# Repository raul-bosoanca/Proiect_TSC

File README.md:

# Proiect_TSC

BOM (Bill of Materials):

| Item | Product Link | Datasheet Link |
|------|-------------|---------------|
| 112A-TAAR-R03 | [Product](https://store.comet.srl.ro/Catalogue/Product/43497/) | [Datasheet](https://store.comet.bg/download-file.php?id=27596) |
| BD5229G-TR | [Product](https://store.comet.srl.ro/Catalogue/Product/43497/) | [Datasheet](https://datasheet.datasheetarchive.com/originals/distributors/Datasheets_SAMA/f2b9741ef86007909f138d561a359946.pdf) |
| Capacitor 0402 | [Product](https://store.comet.srl.ro/Catalogue/Product/43497/) | [Datasheet](https://componentsearchengine.com/Datasheets/2/CC0402MRX5R5BB106.pdf) |
| CPH3225A | [Product](https://store.comet.srl.ro/Catalogue/Product/43497/) | [Datasheet](https://www.snapeda.com/parts/CPH3225A/Seiko%20Instruments/datasheet/) |
| DS3231SN RTC | [Product](https://store.comet.srl.ro/Catalogue/Product/43497/) | [Datasheet](https://www.snapeda.com/parts/DS3231SN%23/Analog%20Devices/datasheet/) |
| ESP32 WROVER 0805 Capacitor | [Product](https://store.comet.srl.ro/Catalogue/Product/43497/) | [Datasheet](https://ro.mouser.com/datasheet/2/40/schottky-3165252.pdf) |
| ESP32 WROVER BME680 Sensor | [Product](https://store.comet.srl.ro/Catalogue/Product/43497/) | [Datasheet](https://www.snapeda.com/parts/BME680/Bosch%20Sensortec/datasheet/) |
| ESP32 WROVER MCP73831 Power Management | [Product](https://store.comet.srl.ro/Catalogue/Product/43497/) | [Datasheet](https://eu.mouser.com/datasheet/2/268/MCP73831_Family_Data_Sheet_DS20001984H-3441711.pdf) |
| ESP32 WROVER P-Channel MOSFET | [Product](https://store.comet.srl.ro/Catalogue/Product/43497/) | [Datasheet](https://www.diodes.com/assets/Datasheets/DMG2305UX.pdf) |
| ESP32C6 Varistor 1812 | [Product](https://store.comet.srl.ro/Catalogue/Product/43497/) | [Datasheet](https://www.tdk-electronics.tdk.com/inf/75/db/CTVS_14/Surge_protection_series.pdf) |
| ESP32-C6 WROOM-1-N8 | [Product](https://store.comet.srl.ro/Catalogue/Product/43497/) | [Datasheet](https://www.snapeda.com/parts/ESP32-C6-WROOM-1-N8/Espressif%20Systems/datasheet/) |
| FH34SRJ-24S-0.5SH Connector | [Product](https://store.comet.srl.ro/Catalogue/Product/43497/) | [Datasheet](https://www.hirose.com/en/product/document?clcode=CL0580-1255-6-99&productname=FH34SRJ-24S-0.5SH(99)&series=FH34SRJ&documenttype=2DDrawing&lang=en&documentid=0000990903) |
| LED Chip 0603 | [Product](https://store.comet.srl.ro/Catalogue/Product/43497/) | [Datasheet](https://www.snapeda.com/parts/KP-1608SURCK/Kingbright/datasheet/) |
| MAX17048G+T10 Battery Fuel Gauge | [Product](https://store.comet.srl.ro/Catalogue/Product/43497/) | [Datasheet](https://www.snapeda.com/parts/MAX17048G+T10/Analog%20Devices/datasheet/) |
| MBR0530 Schottky Diode | [Product](https://store.comet.srl.ro/Catalogue/Product/43497/) | [Datasheet](https://www.snapeda.com/parts/MBR0530/ON%20Semiconductor/datasheet/) |
| PGB1010603MR Inductor | [Product](https://store.comet.srl.ro/Catalogue/Product/43497/) | [Datasheet](https://www.snapeda.com/parts/PGB1010603MR/Littelfuse%20Inc./datasheet/) |
| QWIIC Connector | [Product](https://store.comet.srl.ro/Catalogue/Product/43497/) | [Datasheet](https://www.youtube.com/watch?v=dQw4w9WgXcQ) |
| RCL CPOL 3528 | [Product](https://store.comet.srl.ro/Catalogue/Product/43497/) | [Datasheet](https://s3.amazonaws.com/snapeda/datasheet/TAJB475K025RNJ_AVX.pdf) |
| SI1308EDL-T1-GE3 MOSFET | [Product](https://store.comet.srl.ro/Catalogue/Product/43497/) | [Datasheet](https://www.youtube.com/watch?v=dQw4w9WgXcQ) |
| SJ | [Product](https://store.comet.srl.ro/Catalogue/Product/43497/) | [Datasheet](https://www.youtube.com/watch?v=dQw4w9WgXcQ) |
| TPTP20R | [Product](https://store.comet.srl.ro/Catalogue/Product/43497/) | [Datasheet](https://easyeda.com/component/7524403feb2642ac9f9f26dfb93ceacf) |
| USB4110-GF-A USB Hub | [Product](https://store.comet.srl.ro/Catalogue/Product/43497/) | [Datasheet](https://gct.co/files/drawings/usb4110.pdf) |
| USBLC6-2SC6Y USB Surge Protection | [Product](https://store.comet.srl.ro/Catalogue/Product/43497/) | [Datasheet](https://www.snapeda.com/parts/USBLC6-2SC6Y/STMicroelectronics/datasheet/) |
| XC6220A331MR-G Voltage Regulator | [Product](https://store.comet.srl.ro/Catalogue/Product/43497/) | [Datasheet](https://product.torexsemi.com/system/files/series/xc6220.pdf) |

  Hardware Components:

  ESP32-C3-WROOM:
    
    Wi-Fi/BLE connectivity
    Supports SPI, I2C, and UART communication
    Operates at 3.3V, powered by an LDO regulator

  USB-C - Charging & USB communication
  
  MCP73832 - LiPo battery charging management
  
  LDO 3.3V - Supplies power to ESP32 and peripherals
  
  DC/DC 5V - Provides 5V for sensors
  
  BME680 - Enveroment sensor

ESP32 PINOUT:

    IO0 - RTC INT Signal
    IO1 - CLOCK Signal
    IO2 - SPI MISO Signal
    IO3 - EPD BUSY Signal
    IO4 - SD Card Chip Select
    IO5 - EPD DC Signal
    IO6 - SPI SCK Signal
    IO7 - SPI MOSI Signal
    IO9 - BOOT Button Signal
    IO10 - EPD Chip Select
    IO11 - Flash NOR Memory Chip Select
    IO12 - USB D+ Signal
    IO13 - USB D- Signal
    IO15 - CHANGE Button Signal
    GPIO16 - UART TX
    GPIO17 - UART RX
    IO18 - RTC RESET Signal
    IO19 - I2C Sensor VDDIO Signal
    IO20 - EPD 3V3
    IO21 - I2C SDA Signal
    IO22 - I2C SCL Signal
    IO23 - EPD RESET Signal

Note : On the final 3D models i did not render the top and buttom ground planes because the working pc did not have the power to render them

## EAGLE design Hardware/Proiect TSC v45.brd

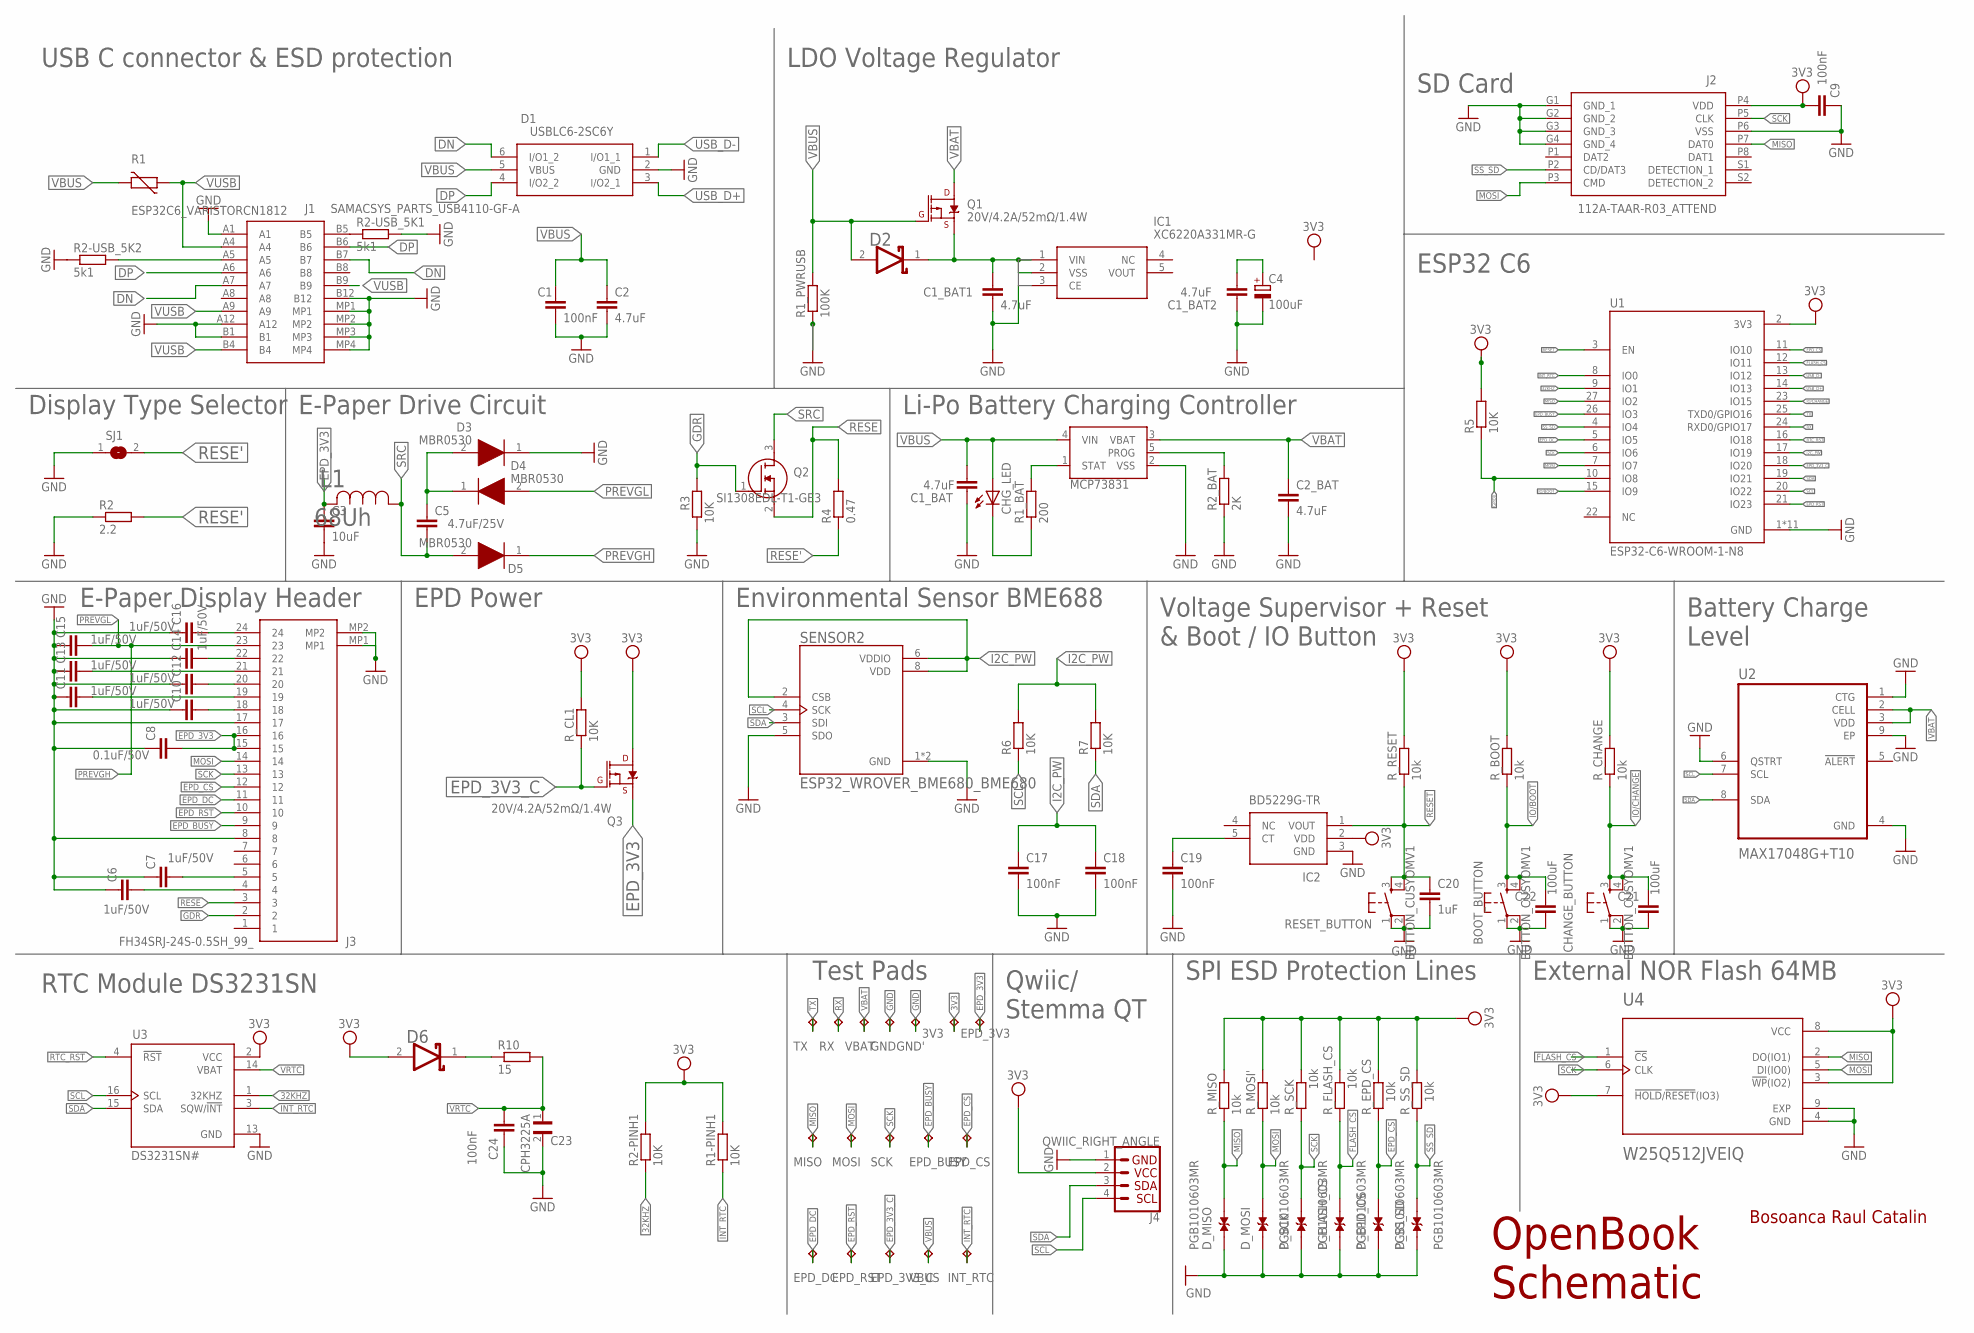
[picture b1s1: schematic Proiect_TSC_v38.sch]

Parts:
3V3: TPTP20R; TP20R
BOOT_BUTTON: BUTTON_CUSYOMV1; MYBUTTON
C1, C9, C17, C18, C19, C23: 100nF; EAGLE-LTSPICE_C0402
C1_BAT, C1_BAT1, C1_BAT2, C2, C2_BAT: 4.7uF; EAGLE-LTSPICE_C0402
C3: 10uF; EAGLE-LTSPICE_C0402
C4: 100uF; RCL_CT3528
C5: 4.7uF/25V; EAGLE-LTSPICE_C0402
C6, C7, C10, C11, C12, C13, C14, C15, C16: 1uF/50V; EAGLE-LTSPICE_C0402
C8: 0.1uF/50V; EAGLE-LTSPICE_C0402
C20: 1uF; EAGLE-LTSPICE_C0402
C21, C22: 100uF; EAGLE-LTSPICE_C0402
C24: CPH3225A; CAPCP3225X100N
CHANGE_BUTTON: BUTTON_CUSYOMV1; MYBUTTON
CHG_LED: ADAFRUIT_LEDCHIP-LED0603; ADAFRUIT_CHIP-LED0603
D1: USBLC6-2SC6Y; SOT95P280X145-6N
D2, D6: ESP32_WROVER_AVX---SD0805S020S1R0_AVX_SD0805S020S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; ESP32_WROVER_AVX---SD0805S020S1R0_AVX_SD0805S020S1R0_0
D3, D4, D5: MBR0530; SOD3716X135N
D_EPD_CS: PGB1010603MR; ESP32_WROVER_AVX---SD0805S020S1R0_AVX_SD0805S020S1R0_0
D_FLASH_CS: PGB1010603MR; ESP32_WROVER_AVX---SD0805S020S1R0_AVX_SD0805S020S1R0_0
D_MISO: PGB1010603MR; ESP32_WROVER_AVX---SD0805S020S1R0_AVX_SD0805S020S1R0_0
D_MOSI: PGB1010603MR; ESP32_WROVER_AVX---SD0805S020S1R0_AVX_SD0805S020S1R0_0
D_SCK: PGB1010603MR; ESP32_WROVER_AVX---SD0805S020S1R0_AVX_SD0805S020S1R0_0
D_SS_SD: PGB1010603MR; ESP32_WROVER_AVX---SD0805S020S1R0_AVX_SD0805S020S1R0_0
EPD_3V3, EPD_3V3_C: TPTP20R; TP20R
EPD_BUSY: TPTP20R; TP20R
EPD_CS: TPTP20R; TP20R
EPD_DC: TPTP20R; TP20R
EPD_RST: TPTP20R; TP20R
GND: TPTP20R; TP20R
GND': TPTP20R; TP20R
IC1: XC6220A331MR-G; SOT95P280X125-5N
IC2: BD5229G-TR; SOT95P280X125-5N
INT_RTC: TPTP20R; TP20R
J1: SAMACSYS_PARTS_USB4110-GF-A; SAMACSYS_PARTS_USB4110GFA
J2: 112A-TAAR-R03_ATTEND; 112ATAARR03ATTEND
J3: FH34SRJ-24S-0.5SH_99_; FH34SRJ24S05SH99
J4: QWIIC_RIGHT_ANGLE; JST04_1MM_RA
L1: 68Uh; IND_4828-WE-TPC_WRE
MCP73831: ESP32_WROVER_SPARKFUN-IC-POWER_MCP73831; ESP32_WROVER_SPARKFUN-IC-POWER_SOT23-5
MISO: TPTP20R; TP20R
MOSI: TPTP20R; TP20R
Q1, Q3: 20V/4.2A/52mΩ/1.4W; ESP32_WROVER_SPARKFUN-DISCRETESEMI_SOT23-3
Q2: SI1308EDL-T1-GE3; SOT65P210X110-3N
R1: ESP32C6_VARISTORCN1812; ESP32C6_VARISTOR_CT/CN1812
R1-PINH1, R2-PINH1, R3, R5, R6, R7: 10K; EAGLE-LTSPICE_C0402
R1_BAT: 200; EAGLE-LTSPICE_C0402
R1_PWRUSB: 100K; EAGLE-LTSPICE_C0402
R2: 2.2; EAGLE-LTSPICE_C0402
R2-USB_5K1, R2-USB_5K2: 5k1; EAGLE-LTSPICE_C0402
R2_BAT: 2K; EAGLE-LTSPICE_C0402
R4: 0.47; EAGLE-LTSPICE_C0402
R10: 15; EAGLE-LTSPICE_C0402
RESET_BUTTON: BUTTON_CUSYOMV1; MYBUTTON
RX: TPTP20R; TP20R
R_BOOT: 10k; EAGLE-LTSPICE_C0402
R_CHANGE: 10k; EAGLE-LTSPICE_C0402
R_CL1: 10K; EAGLE-LTSPICE_C0402
R_EPD_CS: 10k; EAGLE-LTSPICE_C0402
R_FLASH_CS: 10k; EAGLE-LTSPICE_C0402
R_MISO: 10k; EAGLE-LTSPICE_C0402
R_MOSI': 10k; EAGLE-LTSPICE_C0402
R_RESET: 10k; EAGLE-LTSPICE_C0402
R_SCK: 10k; EAGLE-LTSPICE_C0402
R_SS_SD: 10k; EAGLE-LTSPICE_C0402
SCK: TPTP20R; TP20R
SENSOR2: ESP32_WROVER_BME680_BME680; ESP32_WROVER_BME680_PSON80P300X300X100-8N
SJ1: SJ
TX: TPTP20R; TP20R
U1: ESP32-C6-WROOM-1-N8; XCVR_ESP32-C6-WROOM-1-N8
U2: MAX17048G+T10; SON50P200X200X80-9N
U3: DS3231SN#; SOIC127P1032X265-16N
U4: W25Q512JVEIQ; SON127P600X800X80-9N
VBAT: TPTP20R; TP20R
VBUS: TPTP20R; TP20R

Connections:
3V3: 3V3.TP, C9.1, D6.2 (ANODE), IC2.2 (VDD), J2.P4 (VDD), J4.2, Q3.3 (D), R1-PINH1.2, R2-PINH1.2, R5.2, R_BOOT.2, R_CHANGE.2, R_CL1.2, R_EPD_CS.2, R_FLASH_CS.2, R_MISO.2, R_MOSI'.2, R_RESET.2, R_SCK.2, R_SS_SD.2, U1.2 (3V3), U3.2 (VCC), U4.3 (!WP!(IO2)), U4.7 (!HOLD!/!RESET!(IO3)), U4.8 (VCC)
32KHZ: R2-PINH1.1, U1.9 (IO1), U3.1 (32KHZ)
DN: D1.6 (I/O1_2), J1.A7, J1.B7
DP: D1.4 (I/O2_2), J1.A6, J1.B6
EPD_3V3: C3.1, C8.2, EPD_3V3.TP, J3.15, J3.16, L1.2, Q3.2 (S)
EPD_3V3_C: EPD_3V3_C.TP, Q3.1 (G), R_CL1.1, U1.18 (IO20)
EPD_BUSY: EPD_BUSY.TP, J3.9, U1.26 (IO3)
EPD_CS: D_EPD_CS.2, EPD_CS.TP, J3.12, R_EPD_CS.1, U1.11 (IO10)
EPD_DC: EPD_DC.TP, J3.11, U1.5 (IO5)
EPD_RST: EPD_RST.TP, J3.10, U1.21 (IO23)
FLASH_CS: D_FLASH_CS.2, R_FLASH_CS.1, U1.12 (IO11), U4.1 (!CS)
GDR: J3.2, Q2.1 (G), R3.2
GND: BOOT_BUTTON.1, BOOT_BUTTON.2, C1.2, C1_BAT.2, C1_BAT1.2, C1_BAT2.2, C2.2, C2_BAT.2, C3.2, C4.-, C6.1, C7.1, C8.1, C9.2, C10.1, C11.1, C12.1, C13.1, C14.1, C15.1, C16.1, C17.2, C18.2, C19.2, C20.2, C21.2, C22.2, C23.2, C24.2, CHANGE_BUTTON.1, CHANGE_BUTTON.2, D1.2 (GND), D3.1 (K), D_EPD_CS.1, D_FLASH_CS.1, D_MISO.1, D_MOSI.1, D_SCK.1, D_SS_SD.1, GND.TP, GND'.TP, IC2.3 (GND), J1.A1, J1.A12, J1.B1, J1.B12, J1.MP1, J1.MP2, J1.MP3, J1.MP4, J2.G1 (GND_1), J2.G2 (GND_2), J2.G3 (GND_3), J2.G4 (GND_4), J2.P6 (VSS), J3.8, J3.17, J3.MP1, J3.MP2, J4.1, MCP73831.2 (VSS), R1_PWRUSB.1, R2.1, R2-USB_5K1.2, R2-USB_5K2.1, R2_BAT.1, R3.1, RESET_BUTTON.1, RESET_BUTTON.2, SENSOR2.1 (GND), SENSOR2.5 (SDO), SENSOR2.7 (GND), SJ1.1, U1.1 (GND), U1.28 (GND), U1.29_1 (GND), U1.29_2 (GND), U1.29_3 (GND), U1.29_4 (GND), U1.29_5 (GND), U1.29_6 (GND), U1.29_7 (GND), U1.29_8 (GND), U1.29_9 (GND), U2.1 (CTG), U2.4 (GND), U2.6 (QSTRT), U2.9 (EP), U3.13 (GND), U4.4 (GND), U4.9 (EXP)
GPIO8: R5.1, U1.10 (IO8)
I2C_PW: C17.1, C18.1, R6.2, R7.2, SENSOR2.2 (CSB), SENSOR2.6 (VDDIO), SENSOR2.8 (VDD), U1.17 (IO19)
INT_RTC: INT_RTC.TP, R1-PINH1.1, U1.8 (IO0), U3.3 (SQW/!INT)
IO/BOOT: BOOT_BUTTON.3, BOOT_BUTTON.4, C22.1, R_BOOT.1, U1.15 (IO9)
IO/CHANGE: C21.1, CHANGE_BUTTON.3, CHANGE_BUTTON.4, R_CHANGE.1, U1.23 (IO15)
MISO: D_MISO.2, J2.P7 (DAT0), MISO.TP, R_MISO.1, U1.27 (IO2), U4.2 (DO(IO1))
MOSI: D_MOSI.2, J2.P3 (CMD), J3.14, MOSI.TP, R_MOSI'.1, U1.7 (IO7), U4.5 (DI(IO0))
unnamed: C5.1, D3.2 (A), D4.1 (K)
unnamed: CHG_LED.C, R1_BAT.1
unnamed: J1.B5, R2-USB_5K1.1
unnamed: MCP73831.1 (STAT), R1_BAT.2
unnamed: MCP73831.5 (PROG), R2_BAT.2
unnamed: C6.2, J3.4
unnamed: C19.1, IC2.5 (CT)
unnamed: J1.A5, R2-USB_5K2.2
unnamed: D6.1 (CATHODE), R10.1
unnamed: C7.2, J3.5
unnamed: C10.2, J3.18
unnamed: C1_BAT1.1, D2.1 (CATHODE), IC1.1 (VIN), IC1.2 (VSS), Q1.2 (S)
unnamed: C11.2, J3.19
unnamed: C12.2, J3.20
unnamed: C1_BAT2.1, C4.+
unnamed: C14.2, J3.22
unnamed: C16.2, J3.24
PREVGH: C13.2, D5.1 (K), J3.21
PREVGL: C15.2, D4.2 (A), J3.23
RESE: J3.3, Q2.2 (S), R4.2
RESE': R2.2, R4.1, SJ1.2
RESET: C20.1, IC2.1 (VOUT), RESET_BUTTON.3, RESET_BUTTON.4, R_RESET.1, U1.3 (EN)
RTC_RST: U1.16 (IO18), U3.4 (!RST)
RX: RX.TP, U1.24 (RXD0/GPIO17)
SCK: D_SCK.2, J2.P5 (CLK), J3.13, R_SCK.1, SCK.TP, U1.6 (IO6), U4.6 (CLK)
SCL: J4.4, R6.1, SENSOR2.4 (SCK), U1.20 (IO22), U2.7 (SCL), U3.16 (SCL)
SDA: J4.3, R7.1, SENSOR2.3 (SDI), U1.19 (IO21), U2.8 (SDA), U3.15 (SDA)
SRC: C5.2, D5.2 (A), L1.1, Q2.3 (D)
SS_SD: D_SS_SD.2, J2.P2 (CD/DAT3), R_SS_SD.1, U1.4 (IO4)
TX: TX.TP, U1.25 (TXD0/GPIO16)
USB_D+: D1.3 (I/O2_1), U1.14 (IO13)
USB_D-: D1.1 (I/O1_1), U1.13 (IO12)
VBAT: C2_BAT.1, MCP73831.3 (VBAT), Q1.3 (D), U2.2 (CELL), U2.3 (VDD), VBAT.TP
VBUS: C1.1, C1_BAT.1, C2.1, CHG_LED.A, D1.5 (VBUS), D2.2 (ANODE), MCP73831.4 (VIN), Q1.1 (G), R1.2, R1_PWRUSB.2, VBUS.TP
VRTC: C23.1, C24.1, R10.2, U3.14 (VBAT)
VUSB: J1.A4, J1.A9, J1.B4, J1.B9, R1.1

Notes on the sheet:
USB C connector & ESD protection
LDO Voltage Regulator
SD Card
Display Type Selector
E-Paper Drive Circuit
Li-Po Battery Charging Controller
ESP32 C6
E-Paper Display Header
EPD Power
Environmental Sensor BME688
Voltage Supervisor + Reset & Boot / IO Button
Battery Charge Level
RTC Module DS3231SN
Test Pads
Qwiic/ Stemma QT
SPI ESD Protection Lines
External NOR Flash 64MB
Bosoanca Raul Catalin
OpenBook Schematic

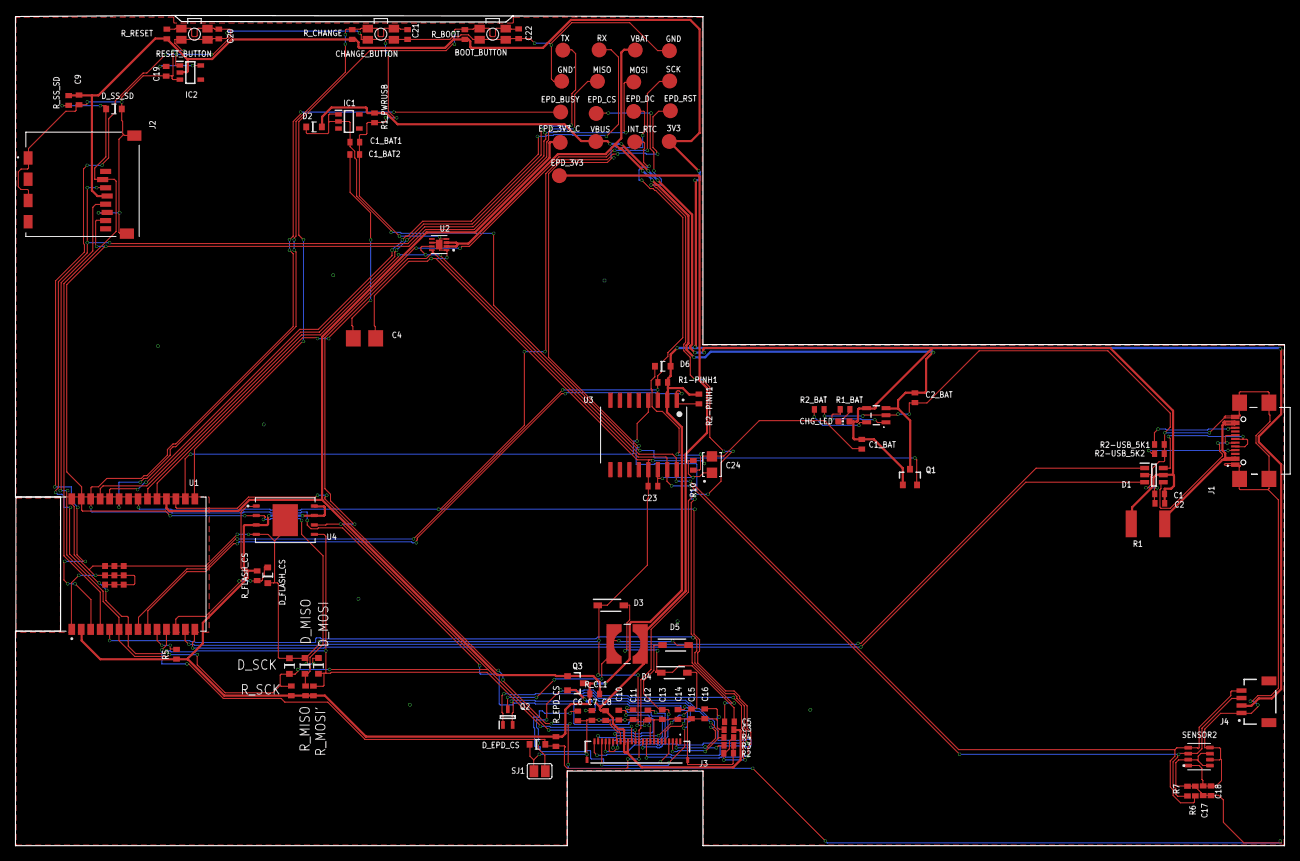
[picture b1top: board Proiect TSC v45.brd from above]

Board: 2 copper layers, 170.2 x 111.3 mm, 103 parts (0 on the bottom side), 56 nets.

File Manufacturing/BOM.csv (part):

Qty,Value,Device,Package,Parts,Description,ARROW_PART_NUMBER,ARROW_PRICE-STOCK,AVAILABILITY,CENTROID_NOT_SPECIFIED,CHECK_PRICES,COPYRIGHT,DATASHEET,DESCRIPTION,DIGIKEY_DESCRIPTION,DIGIKEY_PART_NUMBER,HEIGHT,LEAD_FREE,MANUFACTURER_NAME,MANUFACTURER_PART_NUMBER,MF,MFR_NAME,MOUSER_PART_NUMBER,MOUSER_PRICE-STOCK,MOUSER_TESTING_PART_NUMBER,MOUSER_TESTING_PRICE-STOCK,MP,MPN,PACKAGE,POPULARITY,PREFIX,PRICE,PROD_ID,PURCHASE-URL,ROHS,SNAPEDA_LINK,SPICEMODEL,SPICEPREFIX,TEMPERATURE_RANGE_HIGH,TEMPERATURE_RANGE_LOW,TP_SIGNAL_NAME,VALUE
1,,ADAFRUIT_LEDCHIP-LED0603,ADAFRUIT_CHIP-LED0603,CHG_LED,LED,,,,,,,,,,,,,,,,,,,,,,,,,,,,,,,,,,,,
1,,SJ,SJ,SJ1,"SMD solder JUMPER",,,,,,,,,,,,,,,,,,,,,,,,3,,,,,,,,,,,,
1,0.47,ESP32_WROVER_EAGLE-LTSPICE_RR0402,EAGLE-LTSPICE_C0402,R4,"RESISTOR, European symbol",,,,,,,,,,,,,,,,,,,,,,,,,,,,,,,NONE,R,,,,
1,100K,ESP32_WROVER_EAGLE-LTSPICE_RR0402,EAGLE-LTSPICE_C0402,R1_PWRUSB,"RESISTOR, European symbol",,,,,,,,,,,,,,,,,,,,,,,,,,,,,,,NONE,R,,,,
4,100nF,EAGLE-LTSPICE_CC0402,EAGLE-LTSPICE_C0402,"C17, C18, C19, C23","CAPACITOR, European symbol",,,,,,,,,,,,,,,,,,,,,,,,,,,,,,,NONE,C,,,,
2,100nF,ESP32_WROVER_EAGLE-LTSPICE_CC0402,EAGLE-LTSPICE_C0402,"C1, C9","CAPACITOR, European symbol",,,,,,,,,,,,,,,,,,,,,,,,,,,,,,,NONE,C,,,,
2,100uF,EAGLE-LTSPICE_CC0402,EAGLE-LTSPICE_C0402,"C21, C22","CAPACITOR, European symbol",,,,,,,,,,,,,,,,,,,,,,,,,,,,,,,NONE,C,,,,
1,100uF,RCL_CPOL-EUCT3528,RCL_CT3528,C4,"POLARIZED CAPACITOR, European symbol",,,,,,,,,,,,,,,,,,,,,,,,0,,,,,,,,C,,,,
7,10K,ESP32_WROVER_EAGLE-LTSPICE_RR0402,EAGLE-LTSPICE_C0402,"R1-PINH1, R2-PINH1, R3, R5, R6, R7, R_CL1","RESISTOR, European symbol",,,,,,,,,,,,,,,,,,,,,,,,,,,,,,,NONE,R,,,,
9,10k,ESP32_WROVER_EAGLE-LTSPICE_RR0402,EAGLE-LTSPICE_C0402,"R_BOOT, R_CHANGE, R_EPD_CS, R_FLASH_CS, R_MISO, R_MOSI', R_RESET, R_SCK, R_SS_SD","RESISTOR, European symbol",,,,,,,,,,,,,,,,,,,,,,,,,,,,,,,NONE,R,,,,
1,10uF,ESP32_WROVER_EAGLE-LTSPICE_CC0402,EAGLE-LTSPICE_C0402,C3,"CAPACITOR, European symbol",,,,,,,,,,,,,,,,,,,,,,,,,,,,,,,NONE,C,,,,
1,112A-TAAR-R03_ATTEND,112A-TAAR-R03_ATTEND,112ATAARR03ATTEND,J2,"Micro SD Card Socket, Push-Push Type, Top Mount, SMT, H=1.83mm, 10u",,,,,,,,"Micro SD Card Socket"," Push-Push Type"," Top Mount"," SMT"," H=1.83mm"," 10u",,,1.9mm,,ATTEND,"112A-TAAR-R03 ATTEND",,,,,,,,,,,,,,,,,
1,15,ESP32_WROVER_EAGLE-LTSPICE_RR0402,EAGLE-LTSPICE_C0402,R10,"RESISTOR, European symbol",,,,,,,,,,,,,,,,,,,,,,,,,,,,,,,NONE,R,,,,
1,1uF,EAGLE-LTSPICE_CC0402,EAGLE-LTSPICE_C0402,C20,"CAPACITOR, European symbol",,,,,,,,,,,,,,,,,,,,,,,,,,,,,,,NONE,C,,,,
10,1uF/50V,EAGLE-LTSPICE_CC0402,EAGLE-LTSPICE_C0402,"C6, C7, C8, C10, C11, C12, C13, C14, C15, C16","CAPACITOR, European symbol",,,,,,,,,,,,,,,,,,,,,,,,,,,,,,,NONE,C,,,,
1,2.2,ESP32_WROVER_EAGLE-LTSPICE_RR0402,EAGLE-LTSPICE_C0402,R2,"RESISTOR, European symbol",,,,,,,,,,,,,,,,,,,,,,,,,,,,,,,NONE,R,,,,
1,200,ESP32_WROVER_EAGLE-LTSPICE_RR0402,EAGLE-LTSPICE_C0402,R1_BAT,"RESISTOR, European symbol",,,,,,,,,,,,,,,,,,,,,,,,,,,,,,,NONE,R,,,,
2,20V/4.2A/52mO/1.4W,ESP32_WROVER_SPARKFUN-DISCRETESEMI_MOSFET_PCH-DMG2305UX-7,ESP32_WROVER_SPARKFUN-DISCRETESEMI_SOT23-3,"Q1, Q3","P-channel MOSFETs",,,,,,,,,,,,,,,,,,,,,,,,,,,TRAN-14388,,,,,,,,,20V/4.2A/52mO/1.4W
1,2K,ESP32_WROVER_EAGLE-LTSPICE_RR0402,EAGLE-LTSPICE_C0402,R2_BAT,"RESISTOR, European symbol",,,,,,,,,,,,,,,,,,,,,,,,,,,,,,,NONE,R,,,,
5,4.7uF,ESP32_WROVER_EAGLE-LTSPICE_CC0402,EAGLE-LTSPICE_C0402,"C1_BAT, C1_BAT1, C1_BAT2, C2, C2_BAT","CAPACITOR, European symbol",,,,,,,,,,,,,,,,,,,,,,,,,,,,,,,NONE,C,,,,
1,4.7uF/25V,ESP32_WROVER_EAGLE-LTSPICE_CC0402,EAGLE-LTSPICE_C0402,C5,"CAPACITOR, European symbol",,,,,,,,,,,,,,,,,,,,,,,,,,,,,,,NONE,C,,,,
2,5k1,ESP32_WROVER_EAGLE-LTSPICE_RR0402,EAGLE-LTSPICE_C0402,"R2-USB_5K1, R2-USB_5K2","RESISTOR, European symbol",,,,,,,,,,,,,,,,,,,,,,,,,,,,,,,NONE,R,,,,
1,68Uh,744043680IND_4828-WE-TPC_WRE,IND_4828-WE-TPC_WRE,L1,,,,,,,"Copyright (C) 2024 Ultra Librarian. All rights reserved.",,,,,,,,744043680,,"Wurth Electronics",,,,,,,,,,,,,,,,,,,,
1,BD5229G-TR,BD5229G-TR,SOT95P280X125-5N,IC2,"Voltage Detector with Adjustable Delay Time: CMOS processes are utilized to develop high precision, low current consumption CMOS reset ICs that allow arbitrary setting of the delay time. The extensive lineup includes both Nch Open Drain and CMOS output types in a wide range of detection voltages (from 2.3V to 6.0V, in 0.1V steps), enabling selection of the ideal solution based on customer requirements. In addition, the entire series is of course both lead-free and RoHS-compliant.",,,,,,,,"Voltage Detector with Adjustable Delay Time: CMOS processes are utilized to develop high precision"," low current consumption CMOS reset ICs that allow arbitrary setting of the delay time. The extensive lineup includes both Nch Open Drain and CMOS output types in a wide range of detection voltages (from 2.3V to 6.0V"," in 0.1V steps)"," enabling selection of the ideal solution based on customer requirements. In addition"," the entire series is of course both lead-free and RoHS-compliant.",,,1.25mm,,"ROHM Semiconductor",BD5229G-TR,,,755-BD5229G-TR,https://www.mouser.co.uk/ProductDetail/ROHM-Semiconductor/BD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,,,,,,,,,,,,,,
3,BUTTON_CUSYOMV1,BUTTON_CUSYOMV1,MYBUTTON,"BOOT_BUTTON, CHANGE_BUTTON, RESET_BUTTON",,,,,,,,,,,,,,,,,,,,,,,,,,,,,,,,,,,,,
1,CPH3225A,CPH3225A,CAPCP3225X100N,C24,"Cap 0.011F 3.3V 1210 Flat Check availability",,,"Not in stock",,https://www.snapeda.com/parts/CPH3225A/Seiko+Instruments/vie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,,," 11 mF (EDLC) Supercapacitor 3.3 V 1210 (3225 Metric) - - ",,,,,,,"Seiko Instruments",,,,,,CPH3225A,,"1210 Seiko",,,None,,"https://www.snapeda.com/api/url_track_click_mouser/?unipart_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 Instruments&part_name=CPH3225A&search_term=None",,https://www.snapeda.com/parts/CPH3225A/Seiko+Instruments/vie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,,,,,,
1,DS3231SN#,DS3231SN#,SOIC127P1032X265-16N,U3,"Real Time Clock Serial 16-Pin SOIC W T/R     Check availability",,,"In Stock",,https://www.snapeda.com/parts/DS3231SN%23/Analog+Devices/vie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,,," Extremely Accurate I²C-Integrated RTC/TCXO/Crystal ",,,,,,,"Analog Devices",,,,,,DS3231SN#,,"SOIC-16 Maxim",,,None,,"https://www.snapeda.com/api/url_track_click_mouser/?unipart_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 Devices&part_name=DS3231SN#&search_term=None",,https://www.snapeda.com/parts/DS3231SN%23/Analog+Devices/vie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,,,,,,
1,ESP32-C6-WROOM-1-N8,ESP32-C6-WROOM-1-N8,XCVR_ESP32-C6-WROOM-1-N8,U1,"Check availability",,,"In Stock",,https://www.snapeda.com/parts/ESP32-C6-WROOM-1-N8/Espressif+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,,," Multiprotocol Modules ESP32-C6 module"," Wi-Fi 6 in 2.4 GHz band"," Bluetooth 5"," Zigbee 3.0 and Thread. ESP34-WROOM Compatible - ENGINEERING SAMPLE ",,,,,,,"Espressif Systems",,,,,,ESP32-C6-WROOM-1-N8,,None,,,None,,,,https://www.snapeda.com/parts/ESP32-C6-WROOM-1-N8/Espressif+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,,,
1,ESP32C6_VARISTORCN1812,ESP32C6_VARISTORCN1812,ESP32C6_VARISTOR_CT/CN1812,R1,VARISTOR,,,,,,,,,,,,,,,,,,,,,,,,0,,,,,,,,,,,,
2,ESP32_WROVER_AVX---SD0805S020S1R0_AVX_SD0805S020S1R0_0_0AVX_SD0805S020S1R0_0_0,ESP32_WROVER_AVX---SD0805S020S1R0_AVX_SD0805S020S1R0_0_0AVX_SD0805S020S1R0_0_0,ESP32_WROVER_AVX---SD0805S020S1R0_AVX_SD0805S020S1R0_0,"D2, D6","Schottky Barrier Rectifier Diode",,,,No,,,http://datasheets.avx.com/schottky.pdf,,"DIODE SCHOTTKY 20V 1A 0805",478-7800-1-ND,,yes,,,AVX,,581-SD0805S020S1R0,,,,,,"0805 (2012 metric)",,D,,,,yes,,,,+125°C,-55°C,,
1,ESP32_WROVER_BME680_BME680,ESP32_WROVER_BME680_BME680,ESP32_WROVER_BME680_PSON80P300X300X100-8N,SENSOR2,"Integrated Environmental Unit",,,Unavailable,,,,," Integrated Environmental Unit ",,,,,,,"Bosch Sensortec",,,,,,BME680,,"LGA-8 Bosch Tools",,,None,,,,,,,,,,
1,ESP32_WROVER_SPARKFUN-IC-POWER_MCP73831,ESP32_WROVER_SPARKFUN-IC-POWER_MCP73831,ESP32_WROVER_SPARKFUN-IC-POWER_SOT23-5,MCP73831,"MCP73831T Li-Ion, Li-Pol Controller",,,,,,,,,,,,,,,,,,,,,,,,,,,IC-09995,,,,,,,,,
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
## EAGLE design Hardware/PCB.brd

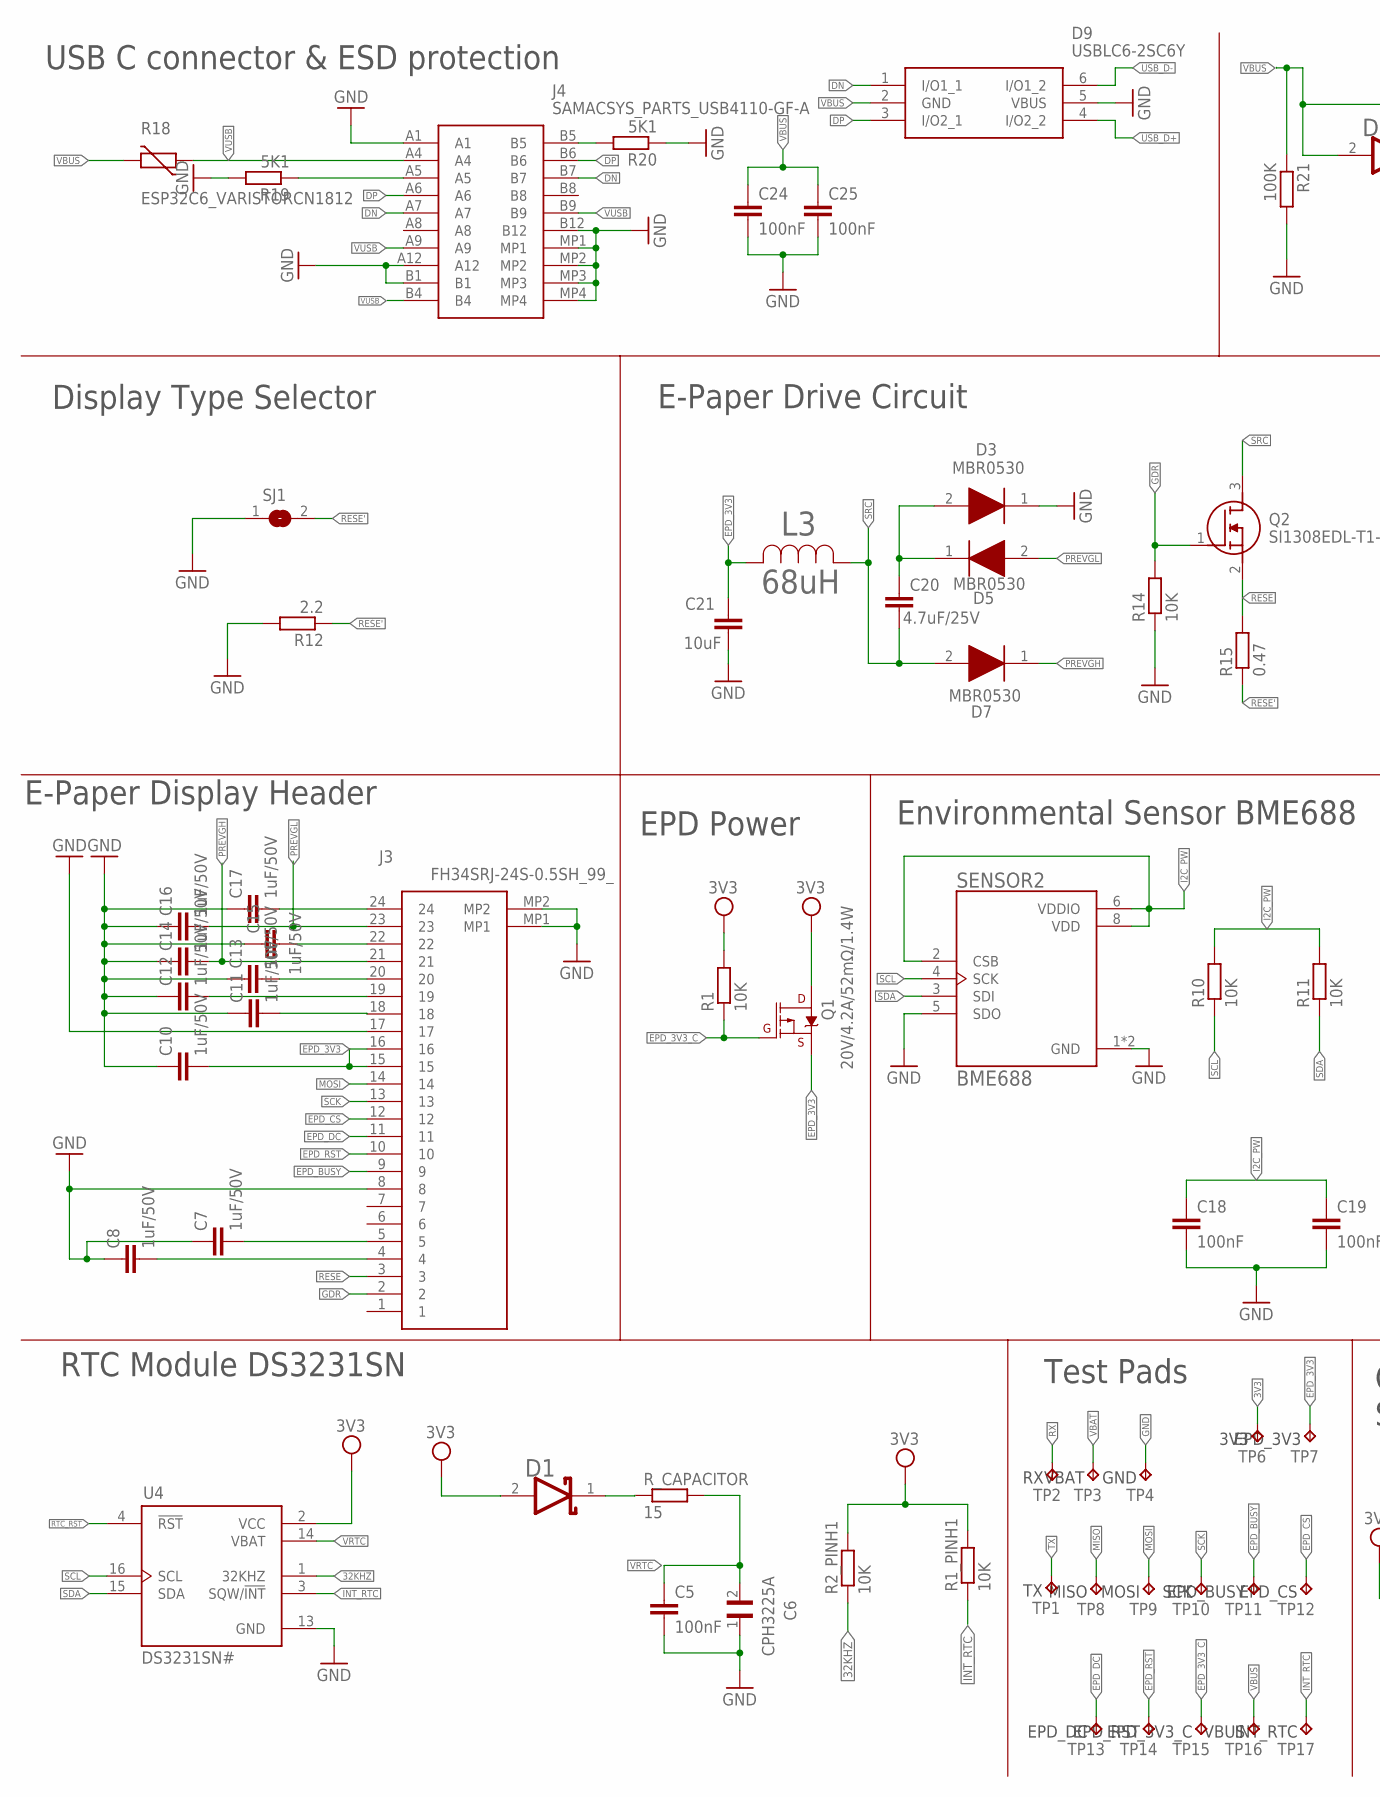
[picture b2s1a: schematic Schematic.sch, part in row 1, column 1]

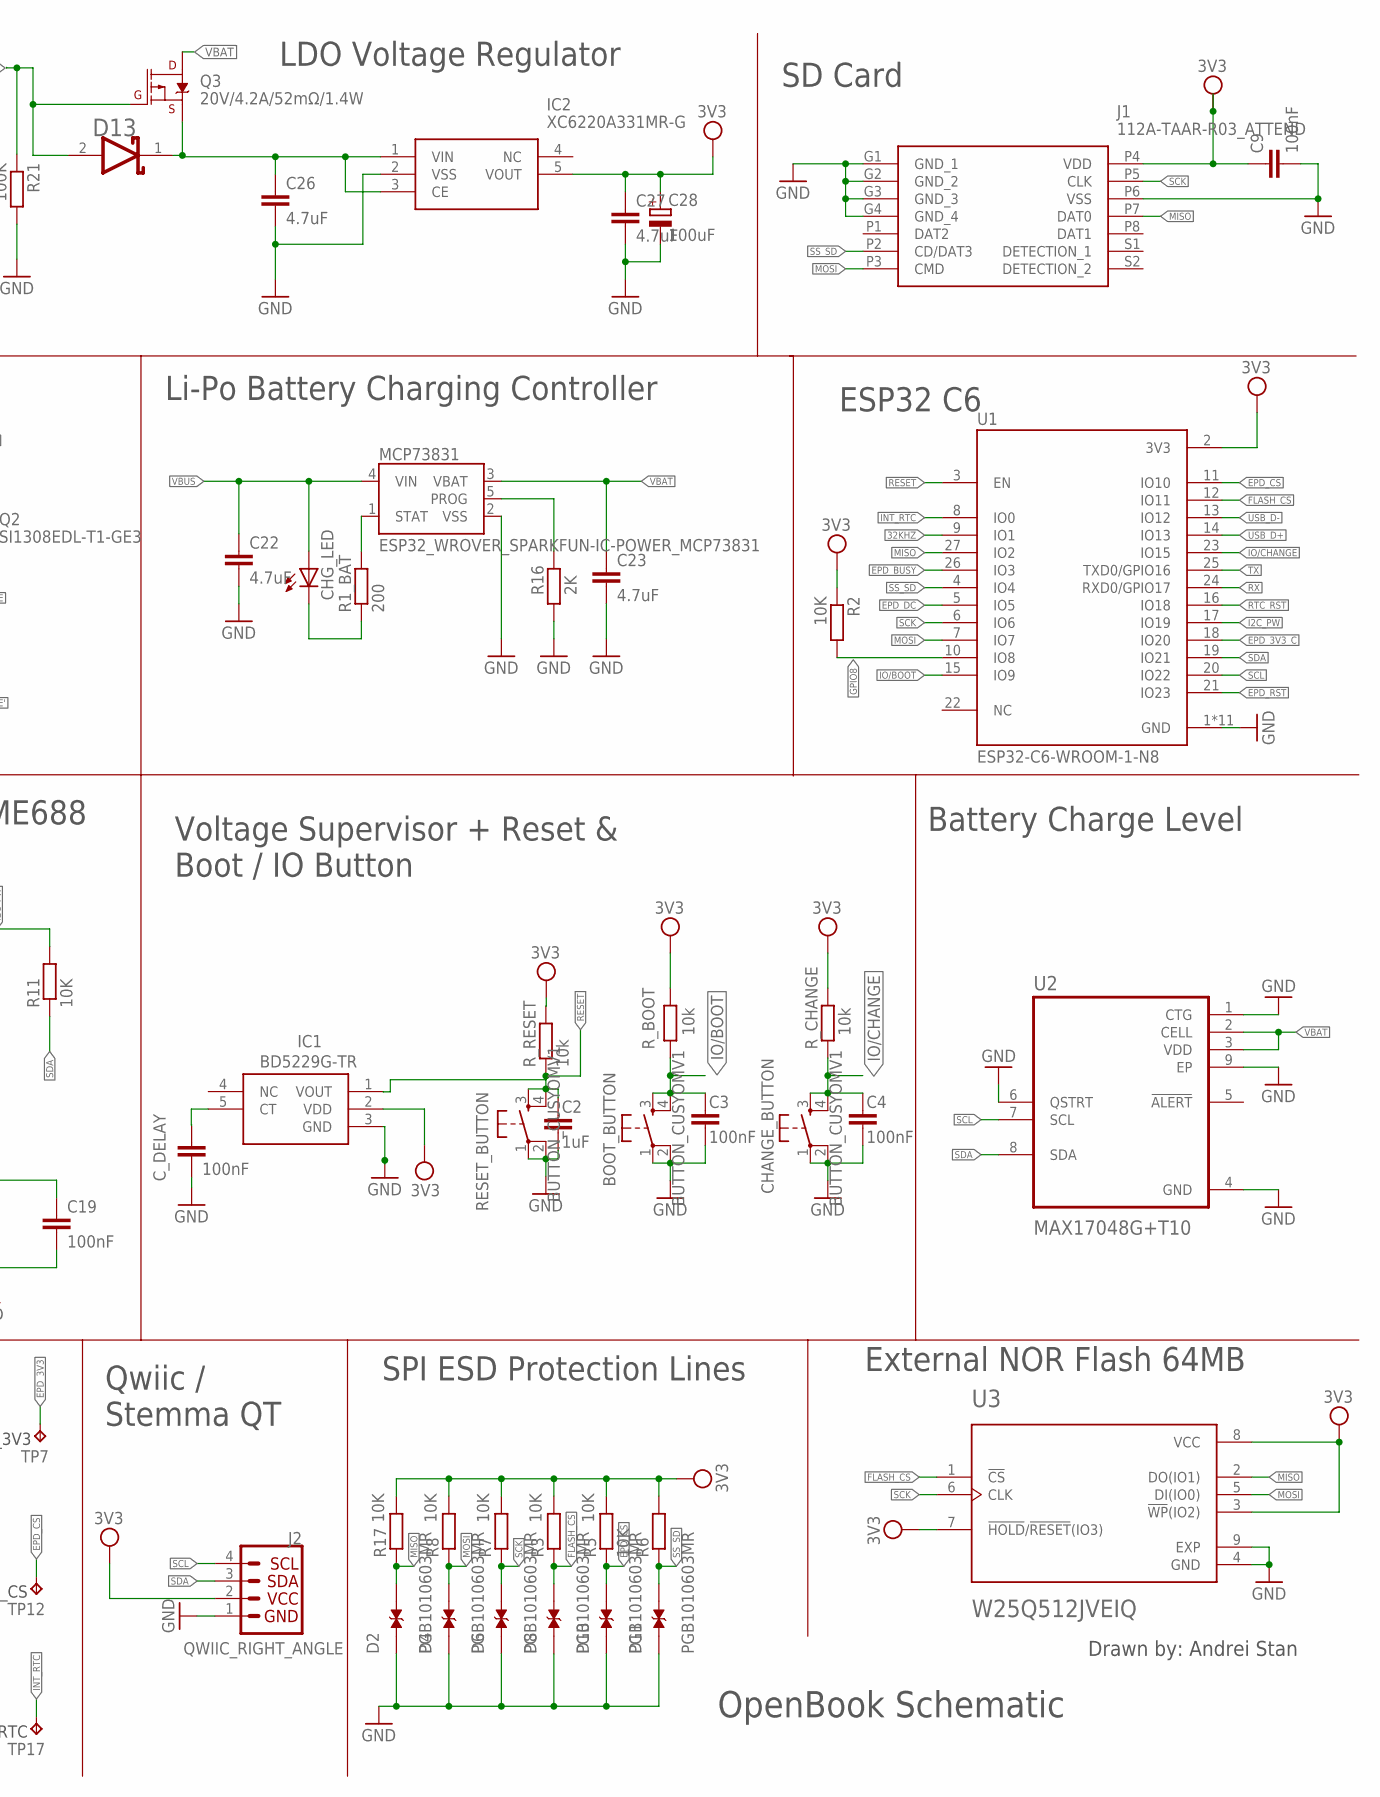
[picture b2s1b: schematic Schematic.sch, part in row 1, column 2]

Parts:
BOOT_BUTTON: BUTTON_CUSYOMV1; MYBUTTON
C2: 1uF; EAGLE-LTSPICE_C0402
C3, C4, C5, C9, C18, C19: 100nF; EAGLE-LTSPICE_C0402
C6: CPH3225A; CAPCP3225X100N
C7, C8, C10, C11, C12, C13, C14, C15, C16, C17: 1uF/50V; EAGLE-LTSPICE_C0402
C20: 4.7uF/25V; ESP32_WROVER_EAGLE-LTSPICE_C0402
C21: 10uF; ESP32_WROVER_EAGLE-LTSPICE_C0402
C22, C23: 4.7uF; EAGLE-LTSPICE_C0402
C24, C25: 100nF; ESP32_WROVER_EAGLE-LTSPICE_C0402
C26, C27: 4.7uF; ESP32_WROVER_EAGLE-LTSPICE_C0402
C28: 100uF; RCL_CT3528
CHANGE_BUTTON: BUTTON_CUSYOMV1; MYBUTTON
CHG_LED: ADAFRUIT_LEDCHIP-LED0603; ADAFRUIT_CHIP-LED0603
C_DELAY: 100nF; EAGLE-LTSPICE_C0402
D1, D13: ESP32_WROVER_AVX---SD0805S020S1R0_AVX_SD0805S020S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; ESP32_WROVER_AVX---SD0805S020S1R0_AVX_SD0805S020S1R0_0
D2, D4, D6, D8, D10, D11: PGB1010603MR; DIOC1608X36N
D3, D5, D7: MBR0530; SOD3716X135N
D9: USBLC6-2SC6Y; SOT95P280X145-6N
IC1: BD5229G-TR; SOT95P280X125-5N
IC2: XC6220A331MR-G; SOT95P280X120-5N
J1: 112A-TAAR-R03_ATTEND; 112ATAARR03ATTEND
J2: QWIIC_RIGHT_ANGLE; JST04_1MM_RA
J3: FH34SRJ-24S-0.5SH_99_; FH34SRJ24S05SH99
J4: SAMACSYS_PARTS_USB4110-GF-A; SAMACSYS_PARTS_USB4110GFA
L3: 68uH; IND_4828-WE-TPC_WRE
MCP73831: ESP32_WROVER_SPARKFUN-IC-POWER_MCP73831; ESP32_WROVER_SPARKFUN-IC-POWER_SOT23-5
Q1, Q3: 20V/4.2A/52mΩ/1.4W; ESP32_WROVER_SPARKFUN-DISCRETESEMI_SOT23-3
Q2: SI1308EDL-T1-GE3; SOT65P210X110-3N
R1, R1_PINH1, R2, R2_PINH1, R3, R5, R6, R7, R8, R10, R11, R14, R17: 10K; ESP32_WROVER_EAGLE-LTSPICE_R0402
R1_BAT: 200; ESP32_WROVER_EAGLE-LTSPICE_R0402
R12: 2.2; ESP32_WROVER_EAGLE-LTSPICE_R0402
R15: 0.47; ESP32_WROVER_EAGLE-LTSPICE_R0402
R16: 2K; ESP32_WROVER_EAGLE-LTSPICE_R0402
R18: ESP32C6_VARISTORCN1812; ESP32C6_VARISTOR_CT/CN1812
R19, R20: 5K1; ESP32_WROVER_EAGLE-LTSPICE_R0402
R21: 100K; ESP32_WROVER_EAGLE-LTSPICE_R0402
RESET_BUTTON: BUTTON_CUSYOMV1; MYBUTTON
R_BOOT: 10k; ESP32_WROVER_EAGLE-LTSPICE_R0402
R_CAPACITOR: 15; ESP32_WROVER_EAGLE-LTSPICE_R0402
R_CHANGE: 10k; ESP32_WROVER_EAGLE-LTSPICE_R0402
R_RESET: 10k; ESP32_WROVER_EAGLE-LTSPICE_R0402
SENSOR2: BME688; ESP32_WROVER_BME680_PSON80P300X300X100-8N
SJ1: SJ
TP1, TP2, TP3, TP4, TP6, TP7, TP8, TP9, TP10, TP11, TP12, TP13, TP14, TP15, TP16, TP17: TPTP20R; TP20R
U1: ESP32-C6-WROOM-1-N8; XCVR_ESP32-C6-WROOM-1-N8
U2: MAX17048G+T10; SON50P200X200X80-9N
U3: W25Q512JVEIQ; SON127P600X800X80-9N
U4: DS3231SN#; SOIC127P1032X265-16N

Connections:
3V3: C9.1, C27.1, C28.+, D1.2 (ANODE), IC1.2 (VDD), IC2.5 (VOUT), J1.P4 (VDD), J2.2, Q1.3 (D), R1.2, R1_PINH1.2, R2.1, R2_PINH1.2, R3.2, R5.2, R6.2, R7.2, R8.2, R17.2, R_BOOT.2, R_CHANGE.2, R_RESET.2, TP6.TP, U1.2 (3V3), U3.3 (!WP!(IO2)), U3.7 (!HOLD!/!RESET!(IO3)), U3.8 (VCC), U4.2 (VCC)
32KHZ: R2_PINH1.1, U1.9 (IO1), U4.1 (32KHZ)
DN: D9.1 (I/O1_1), J4.A7, J4.B7
DP: D9.3 (I/O2_1), J4.A6, J4.B6
EPD_3V3: C10.2, C21.1, J3.15, J3.16, L3.2, Q1.2 (S), TP7.TP
EPD_3V3_C: Q1.1 (G), R1.1, TP15.TP, U1.18 (IO20)
EPD_BUSY: J3.9, TP11.TP, U1.26 (IO3)
EPD_CS: D10.2, J3.12, R5.1, TP12.TP, U1.11 (IO10)
EPD_DC: J3.11, TP13.TP, U1.5 (IO5)
EPD_RST: J3.10, TP14.TP, U1.21 (IO23)
FLASH_CS: D8.2, R3.1, U1.12 (IO11), U3.1 (!CS)
GDR: J3.2, Q2.1 (G), R14.2
GND: BOOT_BUTTON.1, BOOT_BUTTON.2, C2.2, C3.2, C4.2, C5.2, C6.1, C7.1, C8.1, C9.2, C10.1, C11.1, C12.1, C13.1, C14.1, C15.1, C16.1, C17.1, C18.2, C19.2, C21.2, C22.2, C23.2, C24.2, C25.2, C26.2, C27.2, C28.-, CHANGE_BUTTON.1, CHANGE_BUTTON.2, C_DELAY.2, D2.1, D3.1 (K), D4.1, D6.1, D8.1, D9.5 (VBUS), D10.1, D11.1, IC1.3 (GND), IC2.2 (VSS), J1.G1 (GND_1), J1.G2 (GND_2), J1.G3 (GND_3), J1.G4 (GND_4), J1.P6 (VSS), J2.1, J3.8, J3.17, J3.MP1, J3.MP2, J4.A1, J4.A12, J4.B1, J4.B12, J4.MP1, J4.MP2, J4.MP3, J4.MP4, MCP73831.2 (VSS), R12.2, R14.1, R16.1, R19.2, R20.1, R21.2, RESET_BUTTON.1, RESET_BUTTON.2, SENSOR2.1 (GND), SENSOR2.5 (SDO), SENSOR2.7 (GND), SJ1.1, TP4.TP, U1.1 (GND), U1.28 (GND), U1.29_1 (GND), U1.29_2 (GND), U1.29_3 (GND), U1.29_4 (GND), U1.29_5 (GND), U1.29_6 (GND), U1.29_7 (GND), U1.29_8 (GND), U1.29_9 (GND), U2.1 (CTG), U2.4 (GND), U2.6 (QSTRT), U2.9 (EP), U3.4 (GND), U3.9 (EXP), U4.13 (GND)
GPIO8: R2.2, U1.10 (IO8)
I2C_PW: C18.1, C19.1, R10.2, R11.2, SENSOR2.2 (CSB), SENSOR2.6 (VDDIO), SENSOR2.8 (VDD), U1.17 (IO19)
INT_RTC: R1_PINH1.1, TP17.TP, U1.8 (IO0), U4.3 (SQW/!INT)
IO/BOOT: BOOT_BUTTON.3, BOOT_BUTTON.4, C3.1, R_BOOT.1, U1.15 (IO9)
IO/CHANGE: C4.1, CHANGE_BUTTON.3, CHANGE_BUTTON.4, R_CHANGE.1, U1.23 (IO15)
MISO: D2.2, J1.P7 (DAT0), R17.1, TP8.TP, U1.27 (IO2), U3.2 (DO(IO1))
MOSI: D4.2, J1.P3 (CMD), J3.14, R8.1, TP9.TP, U1.7 (IO7), U3.5 (DI(IO0))
unnamed: C_DELAY.1, IC1.5 (CT)
unnamed: D1.1 (CATHODE), R_CAPACITOR.1
unnamed: C8.2, J3.4
unnamed: C7.2, J3.5
unnamed: C20.1, D3.2 (A), D5.1 (K)
unnamed: MCP73831.1 (STAT), R1_BAT.2
unnamed: J4.A5, R19.1
unnamed: CHG_LED.C, R1_BAT.1
unnamed: MCP73831.5 (PROG), R16.2
unnamed: J4.B5, R20.2
unnamed: C26.1, D13.1 (CATHODE), IC2.1 (VIN), IC2.3 (CE), Q3.2 (S)
unnamed: C11.2, J3.18
unnamed: C12.2, J3.19
unnamed: C13.2, J3.20
unnamed: C15.2, J3.22
unnamed: C17.2, J3.24
PREVGH: C14.2, D7.1 (K), J3.21
PREVGL: C16.2, D5.2 (A), J3.23
RESE: J3.3, Q2.2 (S), R15.2
RESE': R12.1, R15.1, SJ1.2
RESET: C2.1, IC1.1 (VOUT), RESET_BUTTON.3, RESET_BUTTON.4, R_RESET.1, U1.3 (EN)
RTC_RST: U1.16 (IO18), U4.4 (!RST)
RX: TP2.TP, U1.24 (RXD0/GPIO17)
SCK: D6.2, J1.P5 (CLK), J3.13, R7.1, TP10.TP, U1.6 (IO6), U3.6 (CLK)
SCL: J2.4, R10.1, SENSOR2.4 (SCK), U1.20 (IO22), U2.7 (SCL), U4.16 (SCL)
SDA: J2.3, R11.1, SENSOR2.3 (SDI), U1.19 (IO21), U2.8 (SDA), U4.15 (SDA)
SRC: C20.2, D7.2 (A), L3.1, Q2.3 (D)
SS_SD: D11.2, J1.P2 (CD/DAT3), R6.1, U1.4 (IO4)
TX: TP1.TP, U1.25 (TXD0/GPIO16)
USB_D+: D9.4 (I/O2_2), U1.14 (IO13)
USB_D-: D9.6 (I/O1_2), U1.13 (IO12)
VBAT: C23.1, MCP73831.3 (VBAT), Q3.3 (D), TP3.TP, U2.2 (CELL), U2.3 (VDD)
VBUS: C22.1, C24.1, C25.1, CHG_LED.A, D9.2 (GND), D13.2 (ANODE), MCP73831.4 (VIN), Q3.1 (G), R18.2, R21.1, TP16.TP
VRTC: C5.1, C6.2, R_CAPACITOR.2, U4.14 (VBAT)
VUSB: J4.A4, J4.A9, J4.B4, J4.B9, R18.1

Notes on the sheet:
OpenBook Schematic
Drawn by: Andrei Stan
External NOR Flash 64MB
Battery Charge Level
ESP32 C6
SD Card
Qwiic / Stemma QT
SPI ESD Protection Lines
Test Pads
RTC Module DS3231SN
E-Paper Display Header
EPD Power
Voltage Supervisor + Reset & Boot / IO Button
Environmental Sensor BME688
Li-Po Battery Charging Controller
E-Paper Drive Circuit
LDO Voltage Regulator
Display Type Selector
USB C connector & ESD protection

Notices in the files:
parts and their libraries:
COPYRIGHT: Copyright (C) 2024 Ultra Librarian. All rights reserved.
